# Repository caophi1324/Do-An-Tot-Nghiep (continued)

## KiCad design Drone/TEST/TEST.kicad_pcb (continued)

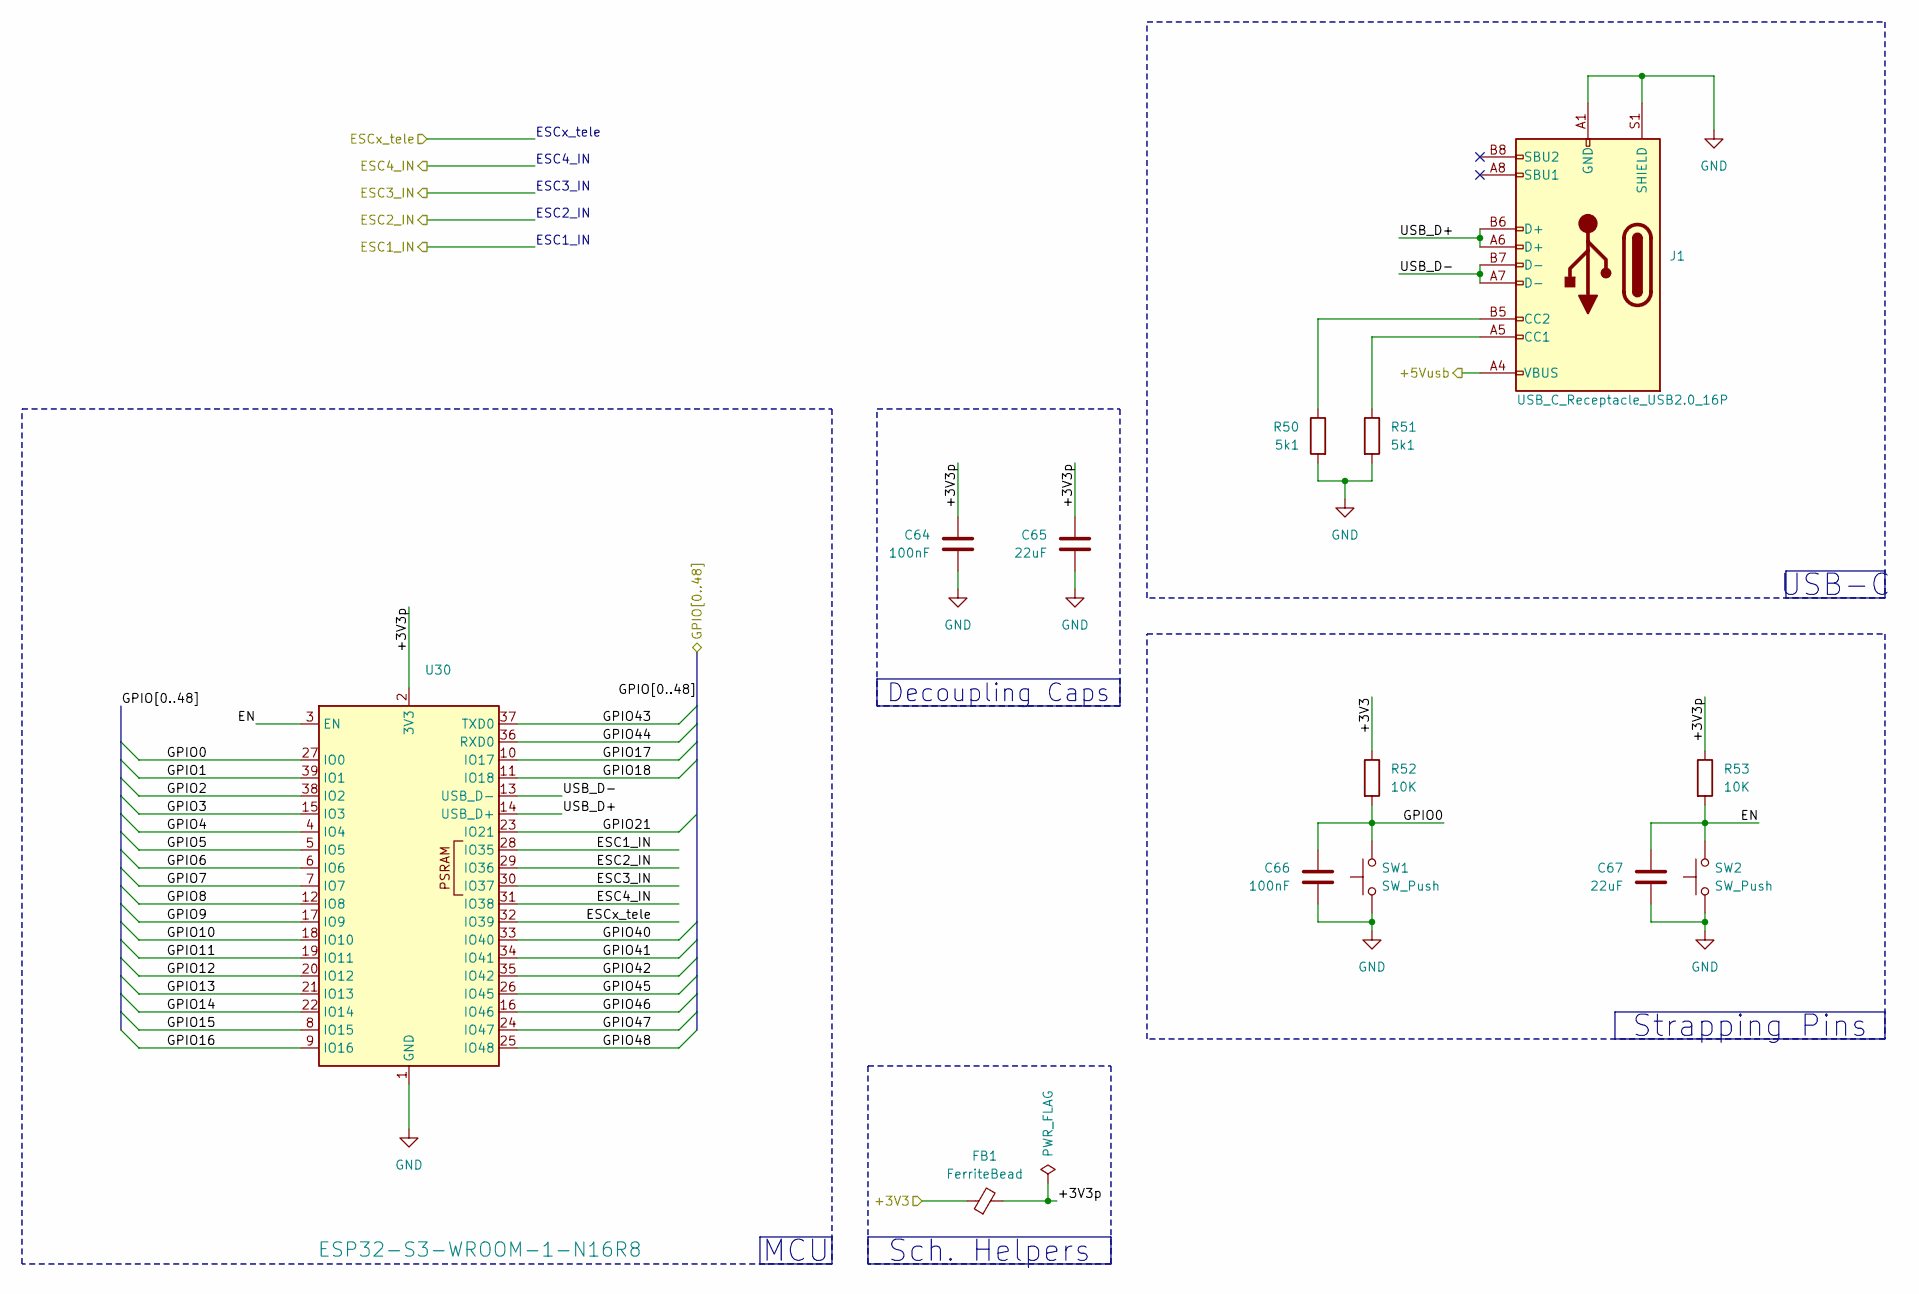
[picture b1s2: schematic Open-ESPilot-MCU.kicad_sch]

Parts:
C64, C66: 100nF; C_0805_2012Metric_Pad1.18x1.45mm_HandSolder; LCSC C49678
C65, C67: 22uF; C_0805_2012Metric_Pad1.18x1.45mm_HandSolder; LCSC C5674
FB1: FerriteBead; L_0805_2012Metric_Pad1.05x1.20mm_HandSolder; LCSC C15957
J1: USB_C_Receptacle_USB2.0_16P; USB_C_Receptacle_HRO_TYPE-C-31-M-12; LCSC C165948
R50, R51: 5k1; R_0805_2012Metric_Pad1.20x1.40mm_HandSolder; LCSC C84375
R52, R53: 10K; R_0805_2012Metric_Pad1.20x1.40mm_HandSolder; LCSC C84376
SW1, SW2: SW_Push; SW_Push_SPST_NO_Alps_SKRK; LCSC C115357
U30: ESP32-S3-WROOM-1-N16R8; ESP32-S3-WROOM-1; LCSC C2913198

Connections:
+3V3: FB1.1, R52.1; also elsewhere on the board
/ESC/ESC1_IN: U30.28 (IO35); also elsewhere on the board
/ESC/ESC2_IN: U30.30 (IO37); also elsewhere on the board
/ESC/ESC3_IN: U30.29 (IO36); also elsewhere on the board
/ESC/ESC4_IN: U30.31 (IO38); also elsewhere on the board
/ESC/ESCx_tele: U30.32 (IO39); also elsewhere on the board
/MCU/+3V3p: C64.1, C65.1, FB1.2, R53.1, U30.2 (3V3)
/MCU/+5Vusb: J1.A4 (VBUS), J1.A9 (VBUS), J1.B4 (VBUS), J1.B9 (VBUS)
/MCU/EN: C67.1, R53.2, SW2.2, U30.3 (EN)
/MCU/GPIO0: C66.1, R52.2, SW1.2, U30.27 (IO0)
/MCU/GPIO1: U30.39 (IO1)
/MCU/GPIO2: U30.38 (IO2); also elsewhere on the board
/MCU/GPIO3: U30.15 (IO3)
/MCU/GPIO4: U30.4 (IO4); also elsewhere on the board
/MCU/GPIO5: U30.5 (IO5)
/MCU/GPIO6: U30.6 (IO6); also elsewhere on the board
/MCU/GPIO7: U30.7 (IO7); also elsewhere on the board
/MCU/GPIO8: U30.12 (IO8); also elsewhere on the board
/MCU/GPIO9: U30.17 (IO9); also elsewhere on the board
/MCU/GPIO10: U30.18 (IO10); also elsewhere on the board
/MCU/GPIO11: U30.19 (IO11); also elsewhere on the board
/MCU/GPIO12: U30.20 (IO12); also elsewhere on the board
/MCU/GPIO13: U30.21 (IO13); also elsewhere on the board
/MCU/GPIO14: U30.22 (IO14); also elsewhere on the board
/MCU/GPIO15: U30.8 (IO15); also elsewhere on the board
/MCU/GPIO16: U30.9 (IO16); also elsewhere on the board
/MCU/GPIO17: U30.10 (IO17); also elsewhere on the board
/MCU/GPIO18: U30.11 (IO18); also elsewhere on the board
/MCU/GPIO21: U30.23 (IO21); also elsewhere on the board
/MCU/GPIO40: U30.33 (IO40)
/MCU/GPIO41: U30.34 (IO41)
/MCU/GPIO42: U30.35 (IO42)
/MCU/GPIO43: U30.37 (TXD0); also elsewhere on the board
/MCU/GPIO44: U30.36 (RXD0); also elsewhere on the board
/MCU/GPIO45: U30.26 (IO45)
/MCU/GPIO46: U30.16 (IO46)
/MCU/GPIO47: U30.24 (IO47); also elsewhere on the board
/MCU/GPIO48: U30.25 (IO48); also elsewhere on the board
/MCU/USB_D+: J1.A6 (D+), J1.B6 (D+), U30.14 (USB_D+)
/MCU/USB_D-: J1.A7 (D-), J1.B7 (D-), U30.13 (USB_D-)
GND: C64.2, C65.2, C66.2, C67.2, J1.A1 (GND), J1.A12 (GND), J1.B1 (GND), J1.B12 (GND), J1.S1 (SHIELD), R50.2, R51.2, SW1.1, SW2.1, U30.1 (GND), U30.40 (GND), U30.41 (GND); also elsewhere on the board
unnamed: J1.A5 (CC1), R51.1
unnamed: J1.B5 (CC2), R50.1

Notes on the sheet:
ESC2_IN
ESC1_IN
ESC3_IN
ESC4_IN
ESCx_tele
Sch. Helpers
Strapping Pins
Decoupling Caps
USB-C
MCU

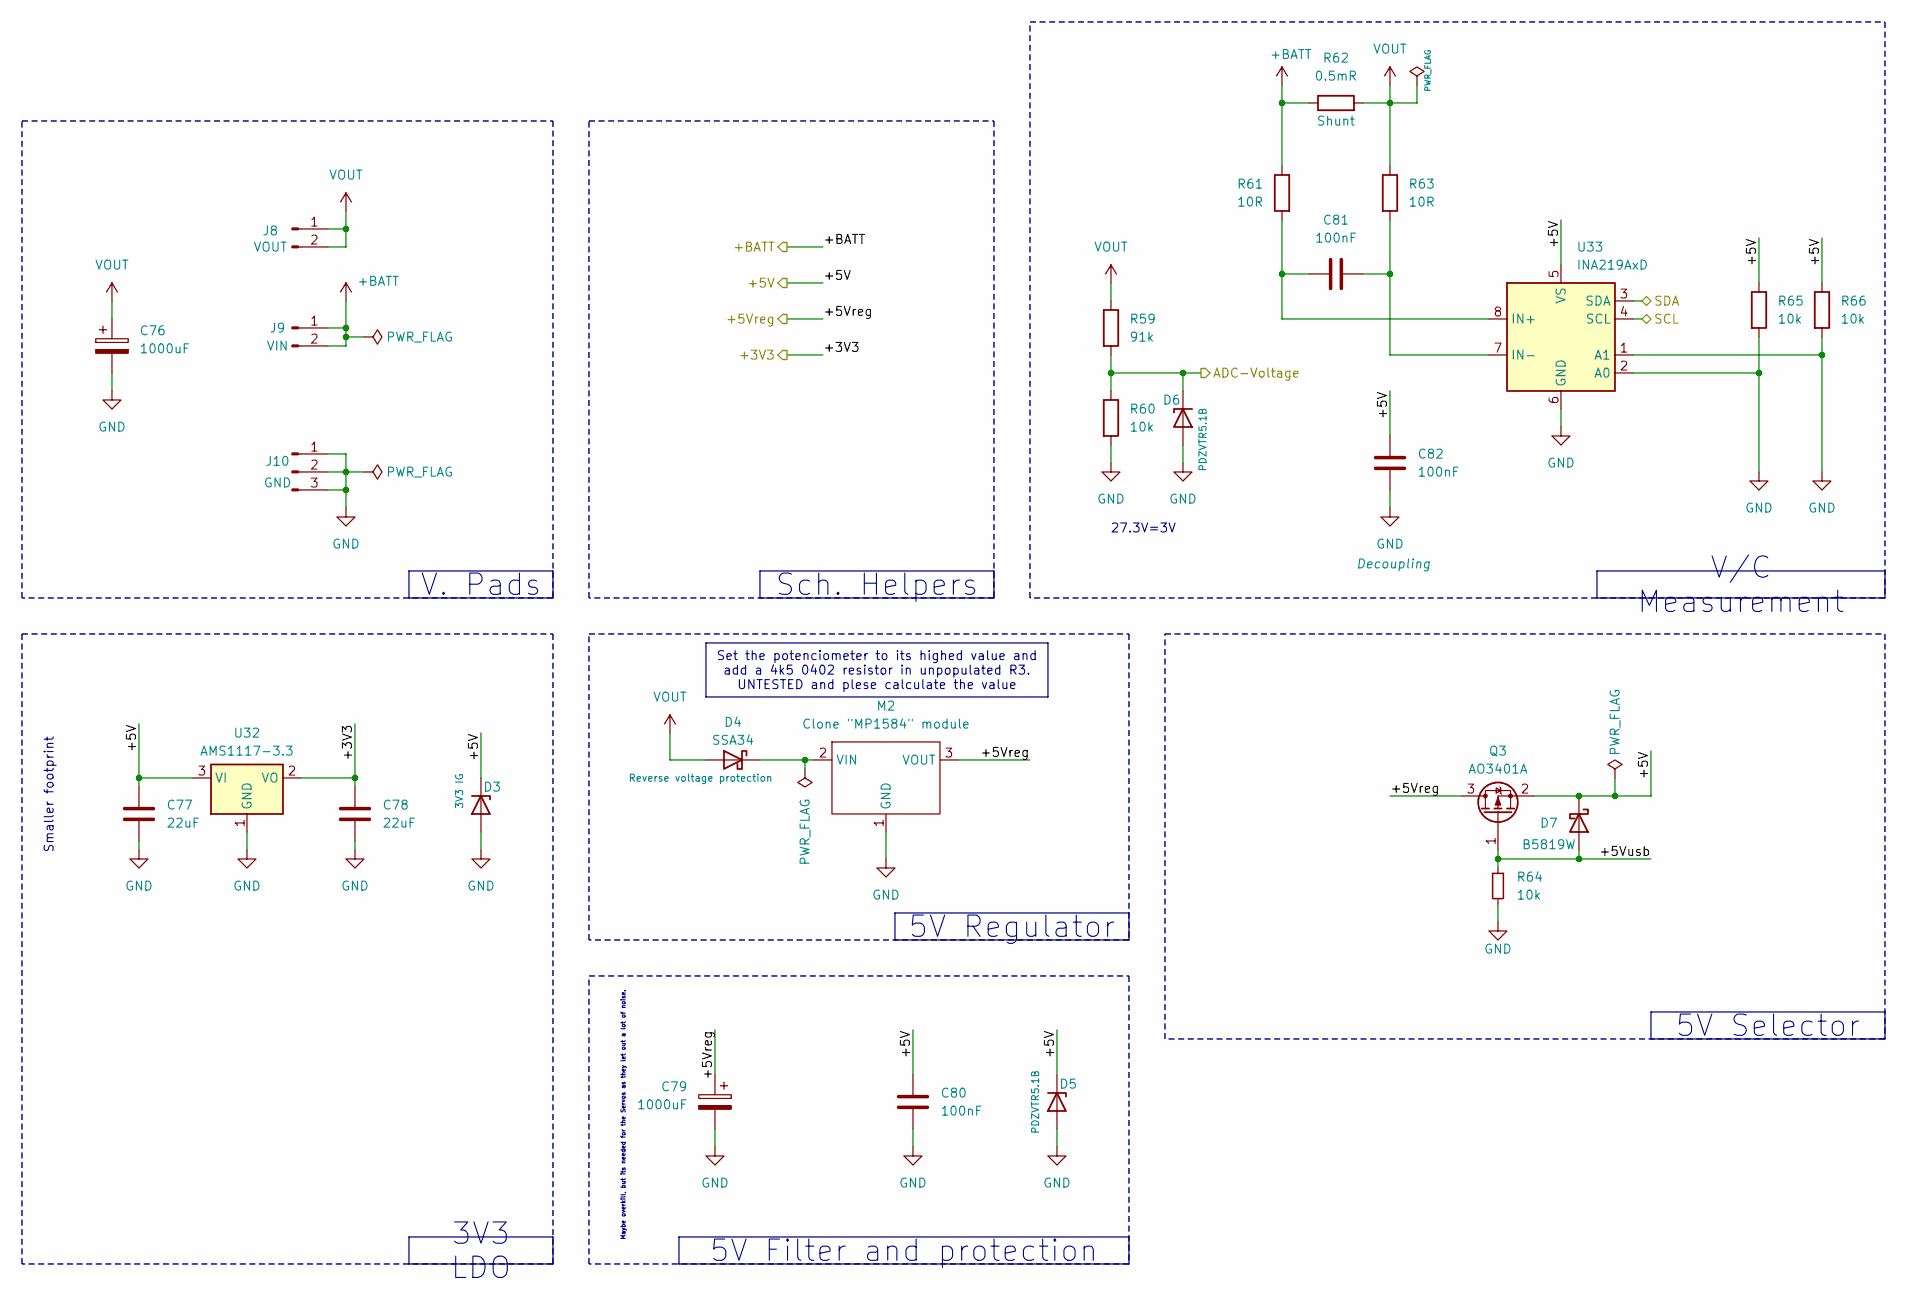
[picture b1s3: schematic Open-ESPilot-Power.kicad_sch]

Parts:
C76: 1000uF; CP_Radial_D10.0mm_P5.00mm; LCSC C398835
C77, C78: 22uF; C_0805_2012Metric_Pad1.18x1.45mm_HandSolder; LCSC C5674
C79: 1000uF; CP_Elec_8x10; LCSC C311227
C80, C81, C82: 100nF; C_0805_2012Metric_Pad1.18x1.45mm_HandSolder; LCSC C49678
D3: 3V3 IG; D_SOD-128
D4: SSA34; D_SMA; LCSC C8678
D5, D6: PDZVTR5.1B; D_SOD-128; LCSC C253499
D7: B5819W; D_SOD-123; LCSC C64885
J8: VOUT; PP_02x
J9: VIN; PP_02x
J10: GND; PP_03x
M2: Clone "MP1584" module; Clone _MP1584_ module
Q3: AO3401A; SOT-23; LCSC C15127
R59: 91k; R_0805_2012Metric_Pad1.20x1.40mm_HandSolder; LCSC C84375
R60, R64, R65, R66: 10k; R_0805_2012Metric_Pad1.20x1.40mm_HandSolder; LCSC C84376
R61, R63: 10R; R_0805_2012Metric_Pad1.20x1.40mm_HandSolder; LCSC C96347
R62: 0.5mR; R_2512_6332Metric_Pad1.40x3.35mm_HandSolder; LCSC C37635712
U32: AMS1117-3.3; SOT-89-3; LCSC C880752
U33: INA219AxD; SOIC-8_3.9x4.9mm_P1.27mm; LCSC C1574856

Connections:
+3V3: C78.1, U32.2 (VO); also elsewhere on the board
+5V: C77.1, C80.1, C82.1, D3.1 (K), D5.1 (K), D7.1 (K), Q3.2 (S), R65.1, R66.1, U32.3 (VI), U33.5 (VS); also elsewhere on the board
+5Vreg: C79.1, M2.3 (VOUT), Q3.3 (D)
+BATT: J9.1, J9.2, R61.1, R62.1; also elsewhere on the board
/MCU/GPIO4: D6.1 (K), R59.2, R60.1; also elsewhere on the board
/MCU/GPIO47: U33.4 (SCL); also elsewhere on the board
/MCU/GPIO48: U33.3 (SDA); also elsewhere on the board
/Power/+5Vusb: D7.2 (A), Q3.1 (G), R64.1
GND: C76.2, C77.2, C78.2, C79.2, C80.2, C82.2, D3.2 (A), D5.2 (A), D6.2 (A), J10.1, J10.2, J10.3, M2.1 (GND), R60.2, R64.2, R65.2, R66.2, U32.1 (GND), U33.1 (A1), U33.2 (A0), U33.6 (GND); also elsewhere on the board
unnamed: D4.1 (K), M2.2 (VIN)
unnamed: C81.1, R61.2, U33.8 (IN+)
unnamed: C81.2, R63.2, U33.7 (IN-)
VOUT: C76.1, D4.2 (A), J8.1, J8.2, R59.1, R62.2, R63.1

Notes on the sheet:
Maybe overkill, but its needed for the Servos as they let out a lot of noise.
27.3V=3V
Smaller footprint
Set the potenciometer to its highed value and add a 4k5 0402 resistor in unpopulated R3. UNTESTED and plese calculate the value
V/C Measurement
5V Filter and protection
5V Selector
3V3 LDO
V. Pads
Sch. Helpers
5V Regulator

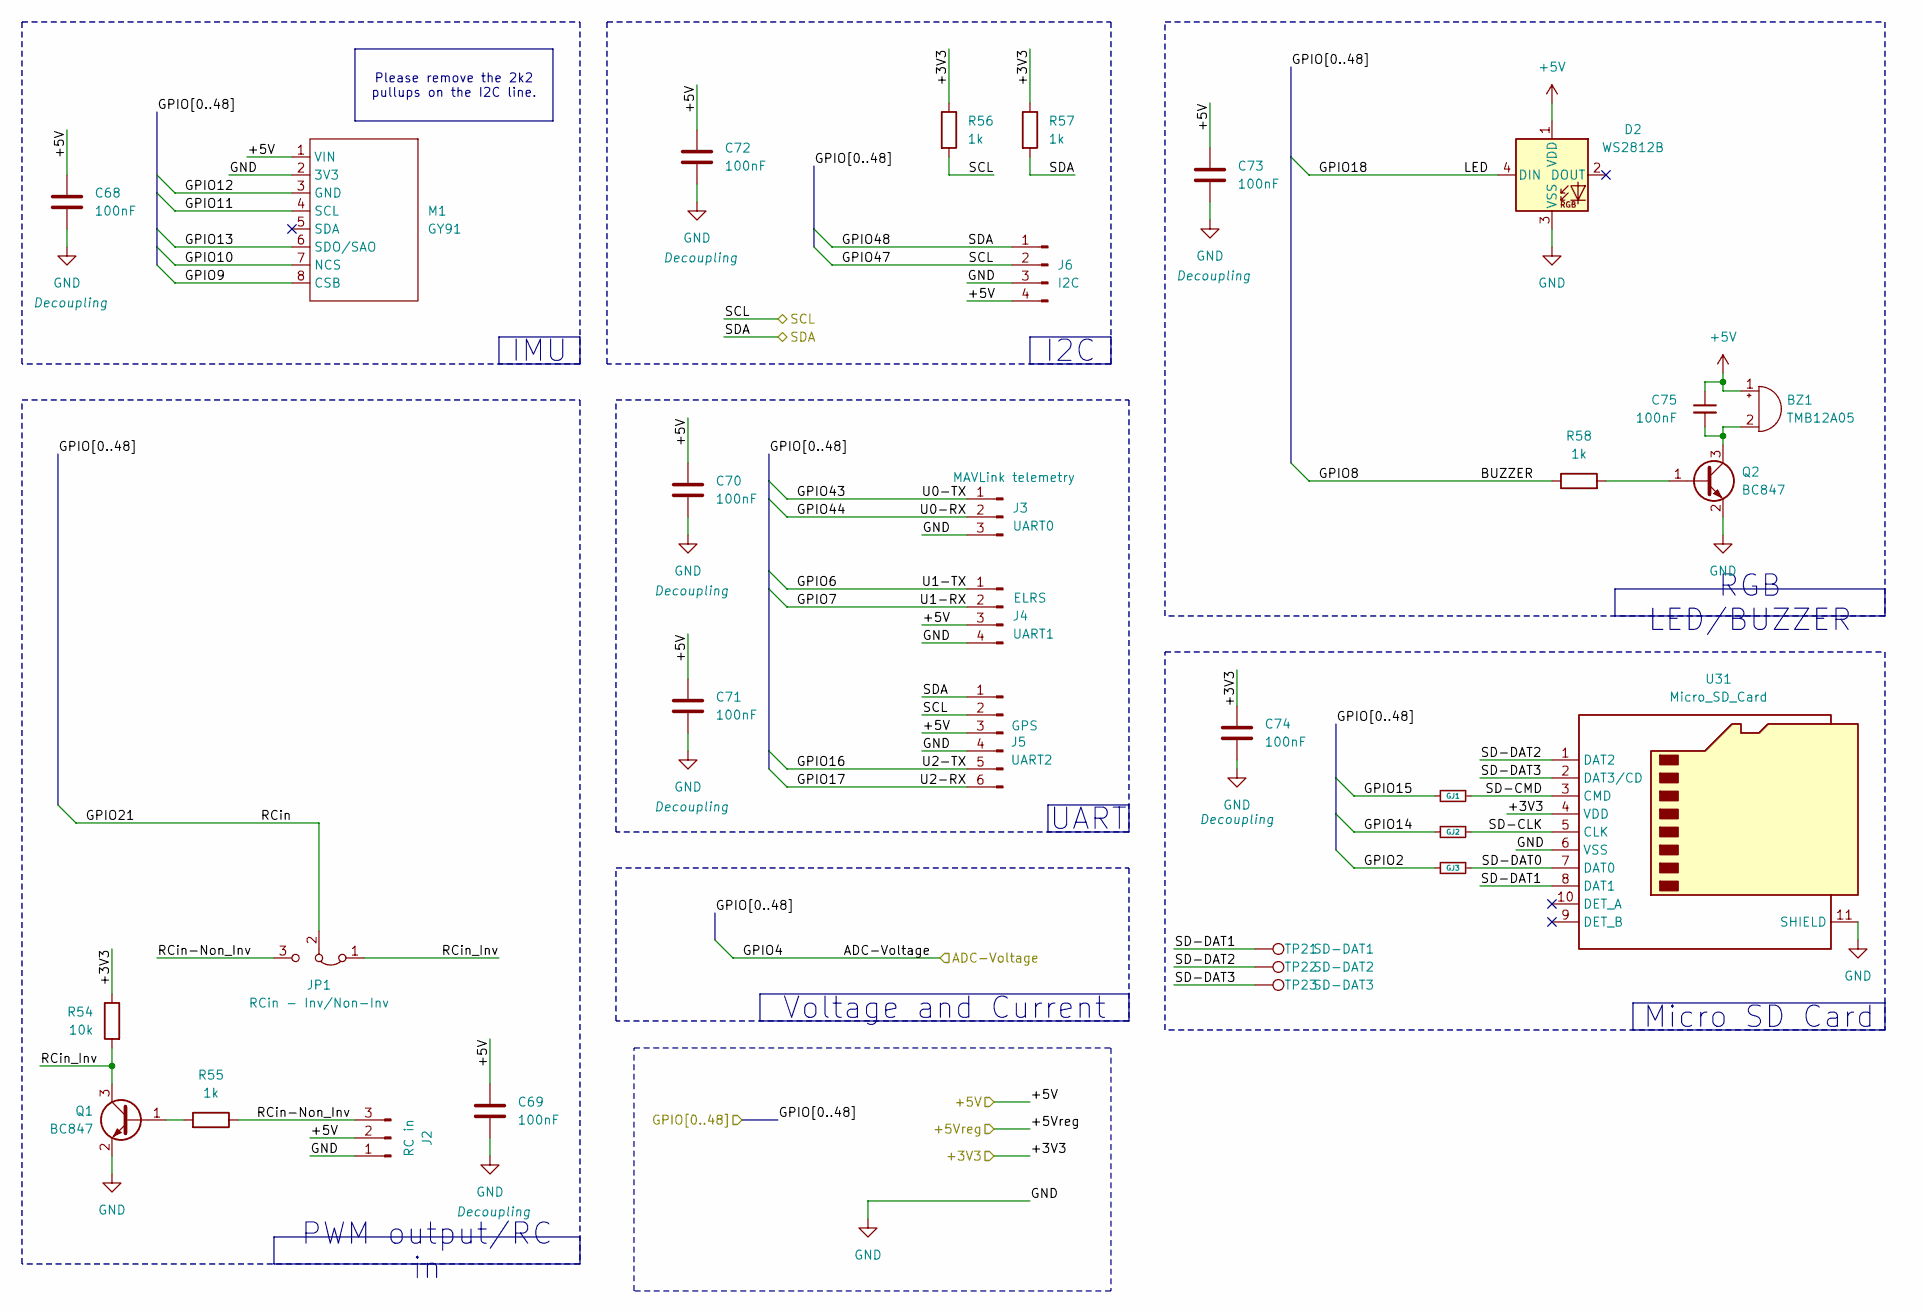
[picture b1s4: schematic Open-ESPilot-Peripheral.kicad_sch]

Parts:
BZ1: TMB12A05; Buzzer_12x9.5RM7.6; LCSC C96093
C68, C69, C70, C71, C72, C73, C74, C75: 100nF; C_0805_2012Metric_Pad1.18x1.45mm_HandSolder; LCSC C49678
D2: WS2812B; LED_WS2812B_PLCC4_5.0x5.0mm_P3.2mm; LCSC C2843785
GJ1, GJ2, GJ3: R_Small; SolderJumper-2_P1.3mm_Bridged2Bar_RoundedPad1.0x1.5mm
J2: RC in; PinHeader_1x03_P2.54mm_Vertical
J3: UART0; PinHeader_1x03_P2.54mm_Vertical
J4: UART1; PinHeader_1x04_P2.54mm_Vertical
J5: UART2; PinHeader_1x06_P2.54mm_Vertical
J6: I2C; PinHeader_1x04_P2.54mm_Vertical
JP1: RCin - Inv/Non-Inv; SolderJumper-3_P1.3mm_Bridged2Bar12_RoundedPad1.0x1.5mm_Num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
M1: GY91; GY-91
Q1, Q2: BC847; SOT-23; LCSC C57668
R54: 10k; R_0805_2012Metric_Pad1.20x1.40mm_HandSolder; LCSC C84376
R55, R56, R57, R58: 1k; R_0805_2012Metric_Pad1.20x1.40mm_HandSolder; LCSC C95781
TP21: SD-DAT1; TestPoint_Pad_D2.0mm
TP22: SD-DAT2; TestPoint_Pad_D2.0mm
TP23: SD-DAT3; TestPoint_Pad_D2.0mm
U31: Micro_SD_Card; microSD_HC_Hirose_DM3AT-SF-PEJM5; LCSC C114218

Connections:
+5V: BZ1.1 (+), C68.1, C69.1, C70.1, C71.1, C72.1, C73.1, C75.1, D2.1 (VDD), J2.2, J4.3, J5.3, J6.4, M1.1 (VIN); also elsewhere on the board
/MCU/GPIO2: GJ3.2; also elsewhere on the board
/MCU/GPIO6: J4.1; also elsewhere on the board
/MCU/GPIO7: J4.2; also elsewhere on the board
/MCU/GPIO8: R58.1; also elsewhere on the board
/MCU/GPIO9: M1.8 (CSB); also elsewhere on the board
/MCU/GPIO10: M1.7 (NCS); also elsewhere on the board
/MCU/GPIO11: M1.4 (SCL); also elsewhere on the board
/MCU/GPIO12: M1.3 (GND); also elsewhere on the board
/MCU/GPIO13: M1.6 (SDO/SAO); also elsewhere on the board
/MCU/GPIO14: GJ2.2; also elsewhere on the board
/MCU/GPIO15: GJ1.2; also elsewhere on the board
/MCU/GPIO16: J5.5; also elsewhere on the board
/MCU/GPIO17: J5.6; also elsewhere on the board
/MCU/GPIO18: D2.4 (DIN); also elsewhere on the board
/MCU/GPIO21: JP1.2 (C); also elsewhere on the board
/MCU/GPIO43: J3.1; also elsewhere on the board
/MCU/GPIO44: J3.2; also elsewhere on the board
/MCU/GPIO47: J5.2, J6.2, R56.2; also elsewhere on the board
/MCU/GPIO48: J5.1, J6.1, R57.2; also elsewhere on the board
/Peripheral/+3V3: C74.1, R54.1, R56.1, R57.1, U31.4 (VDD)
/Peripheral/RCin-Non_Inv: J2.3, JP1.3 (B), R55.1
/Peripheral/RCin_Inv: JP1.1 (A), Q1.3 (C), R54.2
/Peripheral/SD-CLK: GJ2.1, U31.5 (CLK)
/Peripheral/SD-CMD: GJ1.1, U31.3 (CMD)
/Peripheral/SD-DAT0: GJ3.1, U31.7 (DAT0)
/Peripheral/SD-DAT1: TP21.1 (1_1), U31.8 (DAT1)
/Peripheral/SD-DAT2: TP22.1 (1_1), U31.1 (DAT2)
/Peripheral/SD-DAT3: TP23.1 (1_1), U31.2 (DAT3/CD)
GND: C68.2, C69.2, C70.2, C71.2, C72.2, C73.2, C74.2, D2.3 (VSS), J2.1, J3.3, J4.4, J5.4, J6.3, M1.2 (3V3), Q1.2 (E), Q2.2 (E), U31.6 (VSS), U31.11 (SHIELD); also elsewhere on the board
unnamed: BZ1.2 (-), C75.2, Q2.3 (C)
unnamed: Q1.1 (B), R55.2
unnamed: Q2.1 (B), R58.2

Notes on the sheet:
I2C
Micro SD Card
Please remove the 2k2 pullups on the I2C line.
RGB LED/BUZZER
PWM output/RC in
UART
Voltage and Current
IMU

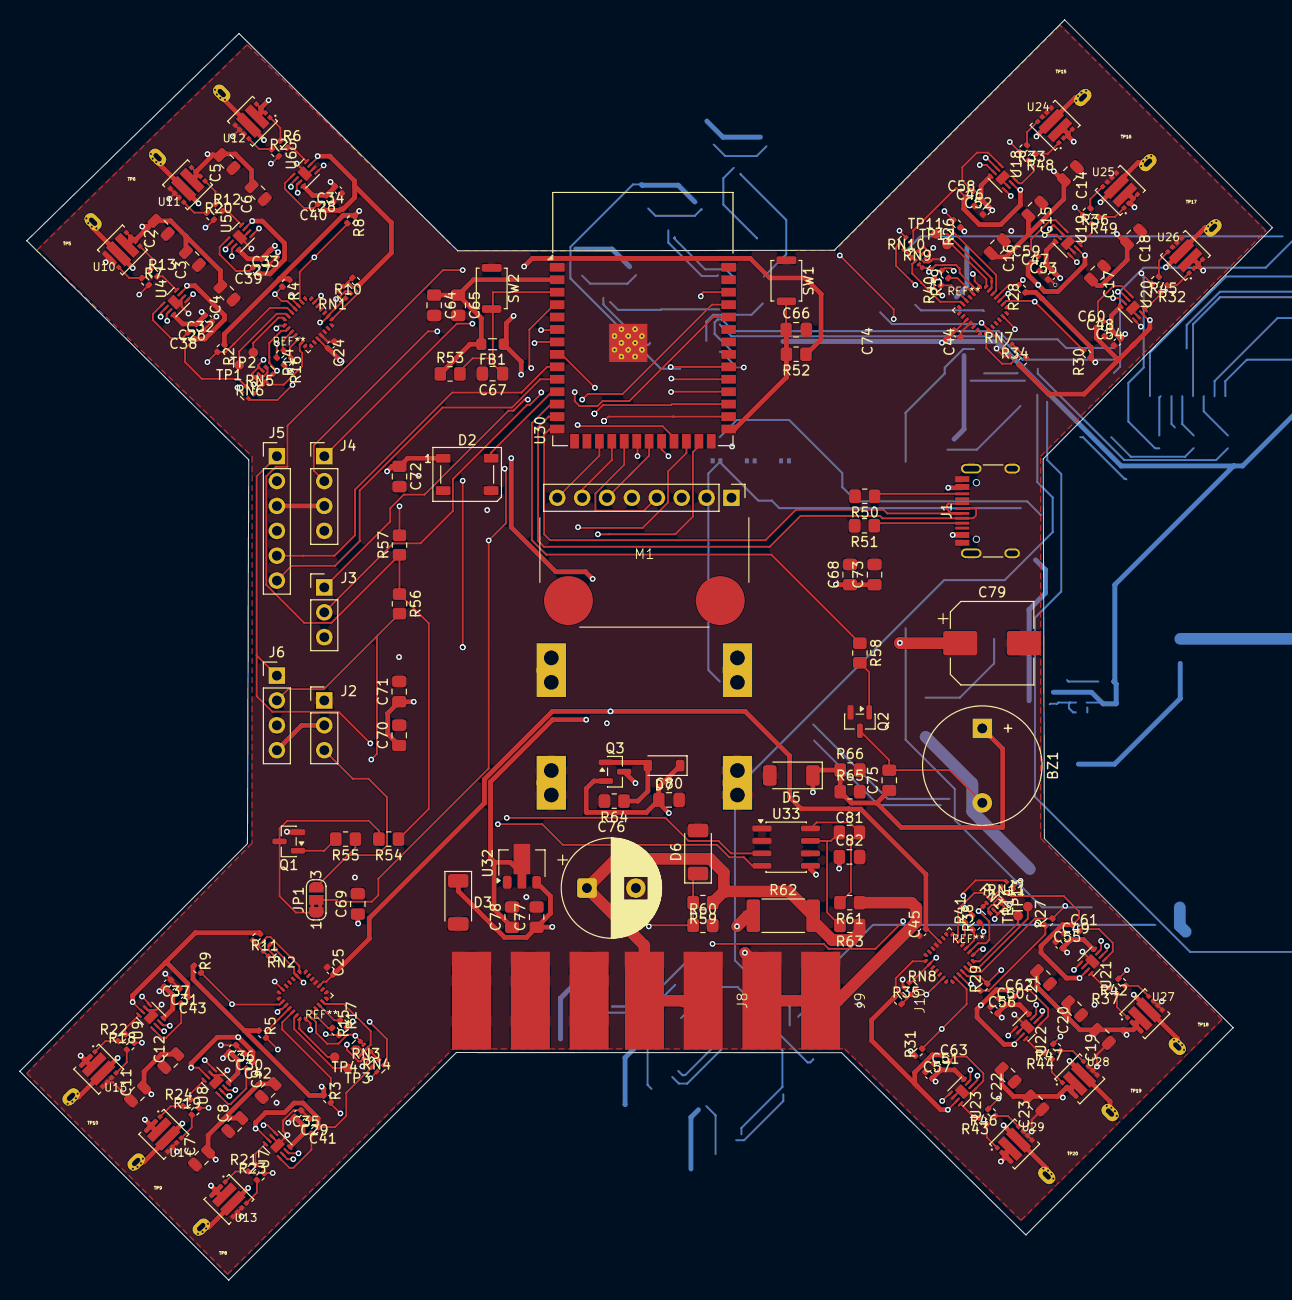
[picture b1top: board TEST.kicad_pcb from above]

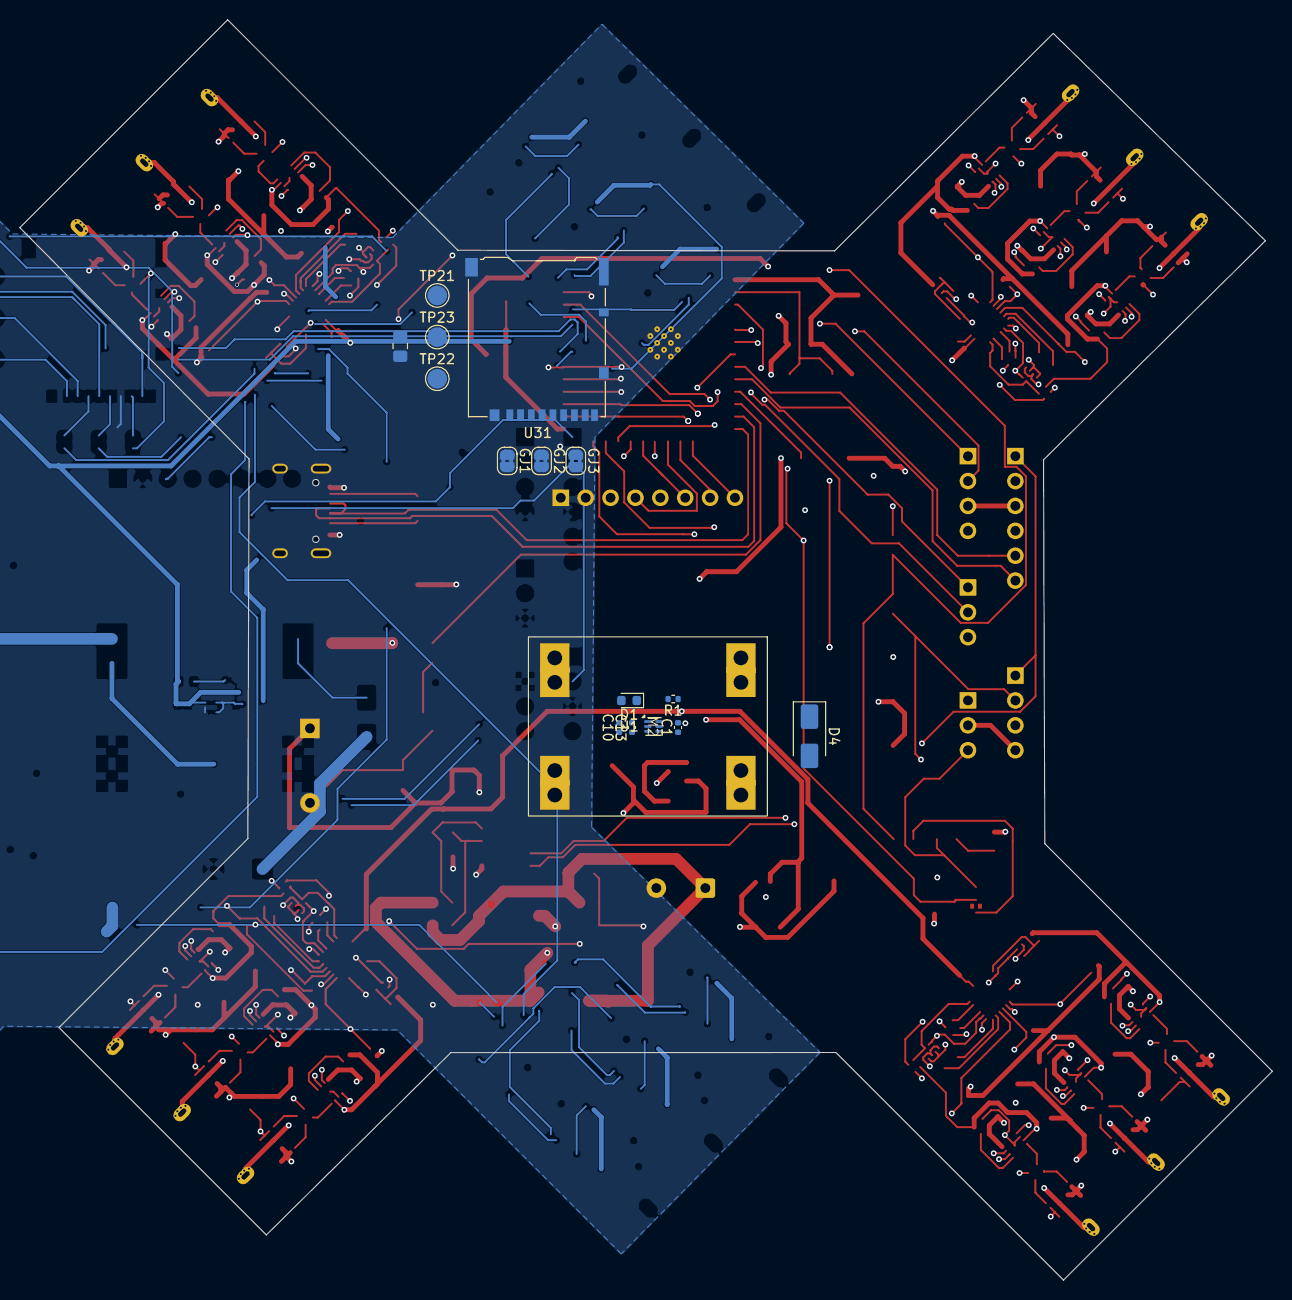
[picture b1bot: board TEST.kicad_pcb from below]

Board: 4 copper layers, 127.9 x 128.7 mm, 245 parts (16 on the bottom side), 185 nets.

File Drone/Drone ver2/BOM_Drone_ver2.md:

# 📋 BOM – Drone ver2 (đọc từ file .kicad_sch)

> [!NOTE]
> Dữ liệu được đọc trực tiếp từ các file KiCad schematic (S-expression format).
> Cấu trúc: `Drone ver2.kicad_sch` (top-level) → 4 sub-sheet bên dưới.
>
> | Sub-sheet | File | Số linh kiện |
> |---|---|---|
> | ESC (4-in-1) | [`ESC.kicad_sch`](file:///D:/TheProject/Drone/Drone%20ver2/Drone%20ver2/ESC.kicad_sch) | 194 |
> | MCU | [`MCU.kicad_sch`](file:///D:/TheProject/Drone/Drone%20ver2/Drone%20ver2/MCU.kicad_sch) | 13 |
> | Peripheral | [`Peripheral.kicad_sch`](file:///D:/TheProject/Drone/Drone%20ver2/Drone%20ver2/Peripheral.kicad_sch) | 37 |
> | Power | [`Open-ESPilot-Power.kicad_sch`](file:///D:/TheProject/Drone/Drone%20ver2/Drone%20ver2/Open-ESPilot-Power.kicad_sch) | 25 |
> | **Tổng** | | **269** |

---

## 🔵 IC / Active Components

| Ref | Linh kiện | Package | LCSC | Sheet |
|---|---|---|---|---|
| U1 | **TPS72733DSE** – LDO 3.3V | WSON-6 1.5×1.5mm | — | ESC |
| U2, U3, U16, U17 | **STM32G071GBU6** – MCU ARM Cortex-M0+ | UFQFPN-28 | — | ESC |
| U4–U9, U18–U23 | **NCP81161MNTBG** – Half-Bridge Gate Driver | DFN-8 2×2mm | — | ESC |
| U34–U45 | **SIZ340BDT-T1-GE3** – Power MOSFET (PowerPAIR) | MOSFET_DT-T1-GE3 | — | ESC |
| U30 | **ESP32-S3-WROOM-1-N16R8** – WiFi/BT MCU chính | ESP32-S3-WROOM-1 | [C2913198](https://www.lcsc.com/product-detail/C2913198.html) | MCU |
| U31 | **Micro_SD_Card** – Thẻ nhớ microSD | Hirose DM3AT | [C114218](https://www.lcsc.com/product-detail/C114218.html) | Peripheral |
| U32 | **AMS1117-3.3** – LDO 3.3V (module phụ) | SOT-89-3 | [C880752](https://www.lcsc.com/product-detail/C880752.html) | Power |
| U33 | **INA219AxD** – Current/Power Monitor I2C | SOIC-8 | [C1574856](https://www.lcsc.com/product-detail/C1574856.html) | Power |

> [!IMPORTANT]
> Schematic dùng **SIZ340BDT** (không phải SIZ200DT như trong file .csv). File `.kicad_sch` là nguồn thiết kế gốc chính xác hơn.

---

## 🟡 Capacitors (Tụ điện)

### Sheet ESC
| Ref | Qty | Giá trị | Package |
|---|---|---|---|
| C1, C10 | 2 | 2.2 µF | C_0805 |
| C2–C9, C11–C12, C14–C23 | 20 | 22 µF | C_0805 dense |
| C13 | 1 | 10 µF | C_0805 |
| C24–C25, C32–C45, C52–C63 | 28 | 100 nF | C_0402 |
| C26–C31, C46–C51 | 12 | 10 µF | C_0402 |

### Sheet MCU
| Ref | Qty | Giá trị | Package | LCSC |
|---|---|---|---|---|
| C64, C66 | 2 | 100 nF | C_0805 HandSolder | [C49678](https://www.lcsc.com/product-detail/C49678.html) |
| C65, C67 | 2 | 22 µF | C_0805 HandSolder | [C5674](https://www.lcsc.com/product-detail/C5674.html) |

### Sheet Peripheral
| Ref | Qty | Giá trị | Package | LCSC |
|---|---|---|---|---|
| C68–C75 | 8 | 100 nF | C_0805 HandSolder | [C49678](https://www.lcsc.com/product-detail/C49678.html) |

### Sheet Power
| Ref | Qty | Giá trị | Package | LCSC |
|---|---|---|---|---|
| C76 | 1 | 1000 µF | CP Radial D10mm | [C398835](https://www.lcsc.com/product-detail/C398835.html) |
| C77, C78 | 2 | 22 µF | C_0805 HandSolder | [C5674](https://www.lcsc.com/product-detail/C5674.html) |
| C79 | 1 | 1000 µF | CP_Elec_8×10 | [C311227](https://www.lcsc.com/product-detail/C311227.html) |
| C80–C82 | 3 | 100 nF | C_0805 HandSolder | [C49678](https://www.lcsc.com/product-detail/C49678.html) |

**Tổng tụ: 82 linh kiện**

---

## 🟠 Resistors (Điện trở)

### Sheet ESC
| Giá trị | Qty | Refs | Package |
|---|---|---|---|
| 1 kΩ | 1 | R1 | 0805 HandSolder |
| 4.7 kΩ | 12 | R2–R5, R8–R9, R26–R31 | 0402 |
| 10 Ω | 24 | R6–R7, R12–R13, R18–R25, R32–R33, R36–R37, R42–R49 | 0402 |
| 10 kΩ | 36 | R10–R11, R34–R35, R67–R98 | 0402 |
| 1 kΩ | 8 | R14–R17, R38–R41 | 0402 |

### Sheet MCU
| Giá trị | Qty | Refs | LCSC |
|---|---|---|---|
| 5.1 kΩ | 2 | R50, R51 | [C84375](https://www.lcsc.com/product-detail/C84375.html) |
| 10 kΩ | 2 | R52, R53 | [C84376](https://www.lcsc.com/product-detail/C84376.html) |

### Sheet Peripheral
| Giá trị | Qty | Refs | LCSC |
|---|---|---|---|
| 10 kΩ | 1 | R54 | [C84376](https://www.lcsc.com/product-detail/C84376.html) |
| 1 kΩ | 4 | R55–R58 | [C95781](https://www.lcsc.com/product-detail/C95781.html) |

### Sheet Power
| Giá trị | Qty | Refs | LCSC |
|---|---|---|---|
| 91 kΩ | 1 | R59 | [C84375](https://www.lcsc.com/product-detail/C84375.html) |
| 10 kΩ | 4 | R60, R64–R66 | [C84376](https://www.lcsc.com/product-detail/C84376.html) |
| 10 Ω | 2 | R61, R63 | [C96347](https://www.lcsc.com/product-detail/C96347.html) |
| 0.5 mΩ (shunt) | 1 | R62 | [C37635712](https://www.lcsc.com/product-detail/C37635712.html) |

**Tổng điện trở: 98 linh kiện**

---

## 🔴 Diodes / LED

| Ref | Linh kiện | Package | LCSC | Sheet |
|---|---|---|---|---|
| D1 | LED (indicator) | LED_0603 | — | ESC |
| D2 | **WS2812B** – RGB LED addressable | PLCC4 5×5mm | [C2843785](https://www.lcsc.com/product-detail/C2843785.html) | Peripheral |
| D3 | 3V3 IG (Zener TVS) | SOD-128 | — | Power |
| D4 | **SSA34** – Schottky 3A 40V | SMA | [C8678](https://www.lcsc.com/product-detail/C8678.html) | Power |
| D5, D6 | **PDZVTR5.1B** – Zener 5.1V | SOD-128 | [C253499](https://www.lcsc.com/product-detail/C253499.html) | Power |
| D7 | **B5819W** – Schottky | SOD-123 | [C64885](https://www.lcsc.com/product-detail/C64885.html) | Power |

---

## ⚡ Transistors / MOSFETs rời

| Ref | Linh kiện | Package | LCSC | Sheet |
|---|---|---|---|---|
| Q1, Q2 | **BC847** – NPN BJT | SOT-23 | [C57668](https://www.lcsc.com/product-detail/C57668.html) | Peripheral |
| Q3 | **AO3401A** – P-CH MOSFET | SOT-23 | [C15127](https://www.lcsc.com/product-detail/C15127.html) | Power |

---

## 🔌 Connectors / Headers

| Ref | Linh kiện | Package | LCSC | Sheet |
|---|---|---|---|---|
| J1 | **USB-C** Receptacle (USB 2.0) | HRO TYPE-C-31-M-12 | [C165948](https://www.lcsc.com/product-detail/C165948.html) | MCU |
| J2 | RC Input (3-pin) | PinHeader 2.54mm 1×3 | — | Peripheral |
| J3 | UART0 (3-pin) | PinHeader 2.54mm 1×3 | — | Peripheral |
| J4 | UART1 (4-pin) | PinHeader 2.54mm 1×4 | — | Peripheral |
| J5 | UART2 (6-pin) | PinHeader 2.54mm 1×6 | — | Peripheral |
| J6 | I2C (4-pin) | PinHeader 2.54mm 1×4 | — | Peripheral |
| J11 | Battery connector | AMASS XT30PW-M | — | Power |

---

## 🔧 Passive / Misc

| Ref | Linh kiện | Package | LCSC | Sheet |
|---|---|---|---|---|
| FB1 | **Ferrite Bead** | 0805 HandSolder | [C15957](https://www.lcsc.com/product-detail/C15957.html) | MCU |
| BZ1 | **TMB12A05** – Buzzer 5V | Buzzer_12x9.5 | [C96093](https://www.lcsc.com/product-detail/C96093.html) | Peripheral |
| SW1, SW2 | **SW_Push** – Nút bấm | Alps SKRK | [C115357](https://www.lcsc.com/product-detail/C115357.html) | MCU |
| M1 | **GY-91** – IMU module (MPU9250+BMP280) | GY-91 footprint | — | Peripheral |
| M2 | **MP1584** – Buck converter module | Clone module | — | Power |
| GJ1–GJ9 | Solder Jumper | 2-pad 1.3mm | — | Peripheral |
| JP1 | Solder Jumper 3-pad | RCin Inv/Non-Inv | — | Peripheral |

---

## ⚪ Test Points

| Nhóm | Refs | Qty | Loại | Sheet |
|---|---|---|---|---|
| Signal TP | TP1–TP4, TP11–TP14 | 8 | TestPoint D1.0mm | ESC |
| Motor pad TP | TP5–TP10, TP15–TP20 | 12 | ESC pad relaxed n4 | ESC |
| SD card TP | TP21 (DAT1), TP22 (DAT2), TP23 (DAT3) | 3 | TestPoint D2.0mm | Peripheral |

---

## 📊 Tổng hợp

| Loại | Số lượng |
|---|---|
| IC (MCU, ESP32, Gate Driver, MOSFET, LDO, Monitor) | 30 |
| Tụ điện | 82 |
| Điện trở | 98 |
| Diodes / LED | 7 |
| Transistor / MOSFET rời | 3 |
| Connectors | 7 |
| Passive khác (Buzzer, Ferrite, SW, IMU, Module) | 7 |
| Solder Jumper | 10 |
| Test Point | 23 |
| **TỔNG** | **267** |

---

## 🗺️ Kiến trúc hệ thống

```mermaid
flowchart TD
    BAT["🔋 Battery\nXT30 (J11)"] --> PWR["Power Sheet\nAMS1117 + INA219\nMP1584 module"]
    PWR --> ESC["ESC Sheet ×4\nSTM32G071 + NCP81161\n+ SIZ340BDT MOSFET"]
    ESC --> MOT["🔄 4× BLDC Motor"]

    PWR --> MCU["MCU Sheet\nESP32-S3-WROOM-1\n+ USB-C"]
    MCU --> PER["Peripheral Sheet\nGY-91 IMU + SD Card\nBuzzer + WS2812B\nUART×3 + I2C"]

    USBC["💻 USB-C (J1)"] --> MCU
```
